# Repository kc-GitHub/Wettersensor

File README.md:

Firmware for Univarsal Wettersensor (Neue Firmware based on the current new version of NewsAskSin Lib)
===================================

* http://www.fhemwiki.de/wiki/Universalsensor
* http://forum.fhem.de/index.php/topic,20620.0.html

#Changelog#

##Version 1.0 (Development)##
 * Rewritten code based on NewsAskSin

##Version 0.15 (Development)##
 * Improve / Fix debugging.
 * Fix [#16](/../../issues/16) so peering with HM-CC-RT-DN should stable now.
 * Add hysteresis for battery voltage measurement.
 * Experimental support for US-100 ultrasonic distance sensor (Do not use this experimental feature if you need the peering with HM-CC-RT-DN at this time)

##Version 0.14##
 * Fix millis() overflow bug. Now, the sensor stays in sleep mode after 49 days, so battery should not drained anymore
 * Battery voltage now measured with 1 digit only.

##Version 0.13 (Beta)##
 * Add new register:
   - transmitTryMax: How often should the sensor try to send data without ack.
   - lowBatLimit: Defined the battery voltage used for low battery detection.
   - ledMode: Switch the device LED on or off while sent out data.
   - altitude: Define the sensor-altitude for calculating the air pressure at sea level.

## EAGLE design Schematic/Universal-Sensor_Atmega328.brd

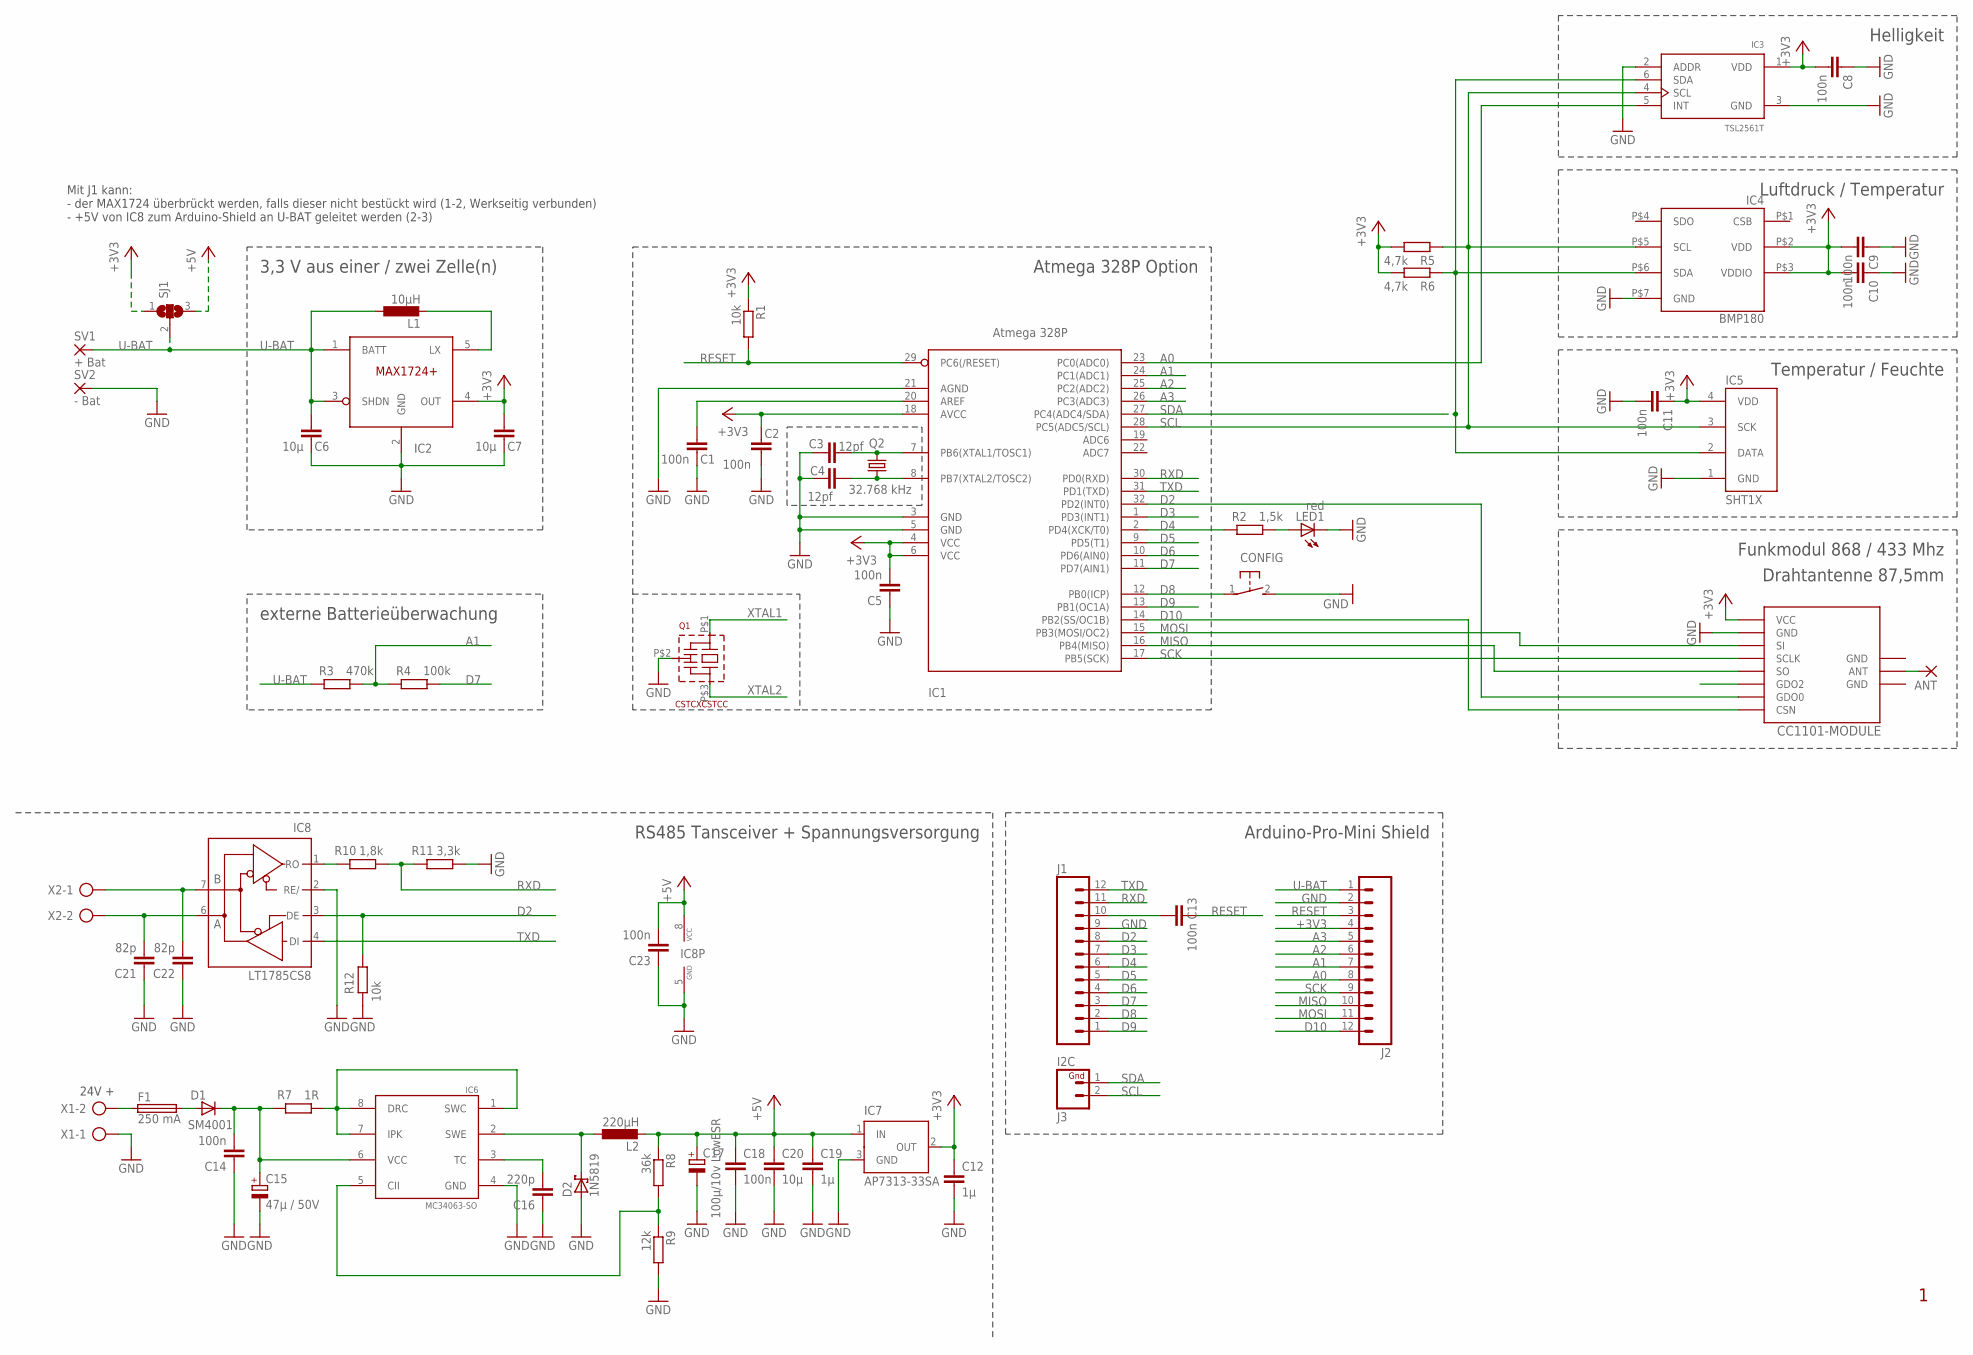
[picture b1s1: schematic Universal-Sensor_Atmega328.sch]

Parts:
ANT: 1,6/0,8
C1, C2, C5, C8, C9, C10, C11, C13, C18, C23: 100n; C0805
C3, C4: 12pf; C0805
C6, C7, C20: 10µ; C1206
C12, C19: 1µ; C0805
C14: 100n; C1206
C15: 47µ / 50V; E2,5-7
C16: 220p; C0805
C17: 100µ/10v LowESR; SMC_D
C21, C22: 82p; C0805
CC1101-MODULE: CC1101_WIRELES_MODULE
CONFIG: DTSM-3
D1: SM4001; MELF-MLL41
D2: 1N5819; SMB
F1: 250 mA; SMD-6,1X2,6
IC1: Atmega 328P; TQFP32-08
IC2: MAX1724; SOT23-5L
IC3: TSL2561T; TMB-6
IC4: BMP180; LGA-7
IC5: SHT1X
IC6: MC34063-SO; SO8
IC7: AP7313-33SA; SOT23
IC8: LT1785CS8; SO08
J1, J2: M12PTH; 1X12
J3: I2C; 1X02
L1: 10µH; L4532P
L2: 220µH; L5650M
LED1: red; CHIP-LED0805
Q1: CSTCXCSTCC; CSTCC
Q2: 32.768 kHz; TC38H
R1, R12: 10k; M0805
R2: 1,5k; M0805
R3: 470k; M0805
R4: 100k; M0805
R5, R6: 4,7k; M0805
R7: 1R; R0805
R8: 36k; R0805
R9: 12k; R0805
R10: 1,8k; R0805
R11: 3,3k; R0805
SJ1: SJ2W; SJ_2
SV1: + Bat; 1,6/0,9
SV2: - Bat; 1,6/0,9
X1, X2: AK550/2

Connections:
+3V3: C2.2, C5.2, C7.2, C8.2, C9.2, C10.2, C11.1, C12.1, CC1101-MODULE.VCC, IC1.4 (VCC), IC1.6 (VCC), IC1.18 (AVCC), IC2.4 (OUT), IC3.1 (VDD), IC4.P$2 (VDD), IC4.P$3 (VDDIO), IC5.4 (VDD), IC7.2 (OUT), J2.4, R1.1, R5.2, R6.2, SJ1.1
+5V: C17.+, C18.1, C19.1, C20.1, C23.2, IC7.1 (IN), IC8.8 (VCC), L2.2, R8.1, SJ1.3
A: C21.2, IC8.6 (A), X2.2
A0: IC1.23 (PC0(ADC0)), IC3.5 (INT), J2.8
A1: IC1.24 (PC1(ADC1)), J2.7, R3.2, R4.1
A2: IC1.25 (PC2(ADC2)), J2.6
A3: IC1.26 (PC3(ADC3)), J2.5
B: C22.2, IC8.7 (B), X2.1
D2: CC1101-MODULE.GDO0, IC1.32 (PD2(INT0)), IC8.3 (DE), J1.8, R12.2
D3: IC1.1 (PD3(INT1)), J1.7
D4: IC1.2 (PD4(XCK/T0)), J1.6, R2.1
D5: IC1.9 (PD5(T1)), J1.5
D6: IC1.10 (PD6(AIN0)), J1.4
D7: IC1.11 (PD7(AIN1)), J1.3, R4.2
D8: CONFIG.1, IC1.12 (PB0(ICP)), J1.2
D9: IC1.13 (PB1(OC1A)), J1.1
D10: CC1101-MODULE.CSN, IC1.14 (PB2(SS/OC1B)), J2.12
GND: C1.1, C2.1, C3.2, C4.2, C5.1, C6.1, C7.1, C8.1, C9.1, C10.1, C11.2, C12.2, C14.1, C15.-, C16.1, C17.-, C18.2, C19.2, C20.2, C21.1, C22.1, C23.1, CC1101-MODULE.GND@1 (GND), CC1101-MODULE.GND@2 (GND), CC1101-MODULE.GND@3 (GND), CONFIG.2, D2.A, IC1.3 (GND), IC1.5 (GND), IC1.21 (AGND), IC2.2 (GND), IC3.2 (ADDR), IC3.3 (GND), IC4.P$7 (GND), IC5.1 (GND), IC6.4 (GND), IC7.3 (GND), IC8.2 (RE/), IC8.5 (GND), J1.9, J2.2, LED1.C, Q1.P$2 (GND), R9.2, R11.1, R12.1, SV2.1, X1.1
MISO: CC1101-MODULE.SO, IC1.16 (PB4(MISO)), J2.10
MOSI: CC1101-MODULE.SI, IC1.15 (PB3(MOSI/OC2)), J2.11
unnamed: C13.2, J1.10
unnamed: IC2.5 (LX), L1.2
unnamed: LED1.A, R2.2
unnamed: ANT.1, CC1101-MODULE.ANT
unnamed: F1.1, X1.2
unnamed: IC8.1 (RO), R10.2
unnamed: C1.2, IC1.20 (AREF)
unnamed: D1.A, F1.2
unnamed: IC6.1 (SWC), IC6.7 (IPK), IC6.8 (DRC), R7.1
unnamed: C14.2, C15.+, D1.C, IC6.6 (VCC), R7.2
unnamed: IC6.5 (CII), R8.2, R9.1
unnamed: C16.2, IC6.3 (TC)
unnamed: D2.C, IC6.2 (SWE), L2.1
RESET: C13.1, IC1.29 (PC6(/RESET)), J2.3, R1.2
RXD: IC1.30 (PD0(RXD)), J1.11, R10.1, R11.2
SCK: CC1101-MODULE.SCLK, IC1.17 (PB5(SCK)), J2.9
SCL: IC1.28 (PC5(ADC5/SCL)), IC3.4 (SCL), IC4.P$5 (SCL), IC5.3 (SCK), J3.2, R5.1
SDA: IC1.27 (PC4(ADC4/SDA)), IC3.6 (SDA), IC4.P$6 (SDA), IC5.2 (DATA), J3.1, R6.1
TXD: IC1.31 (PD1(TXD)), IC8.4 (DI), J1.12
U-BAT: C6.2, IC2.1 (BATT), IC2.3 (SHDN), J2.1, L1.1, R3.1, SJ1.2, SV1.1
XTAL1: C3.1, IC1.7 (PB6(XTAL1/TOSC1)), Q1.P$1 (1), Q2.2
XTAL2: C4.1, IC1.8 (PB7(XTAL2/TOSC2)), Q1.P$3 (3), Q2.1

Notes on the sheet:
Mit J1 kann: - der MAX1724 überbrückt werden, falls dieser nicht bestückt wird (1-2, Werkseitig verbunden) - +5V von IC8 zum Arduino-Shield an U-BAT geleitet werden (2-3)
24V +
RS485 Tansceiver + Spannungsversorgung
3,3 V aus einer / zwei Zelle(n)
externe Batterieüberwachung
Arduino-Pro-Mini Shield
Atmega 328P Option
Helligkeit
Luftdruck / Temperatur
Temperatur / Feuchte
Funkmodul 868 / 433 Mhz
Drahtantenne 87,5mm
IC2

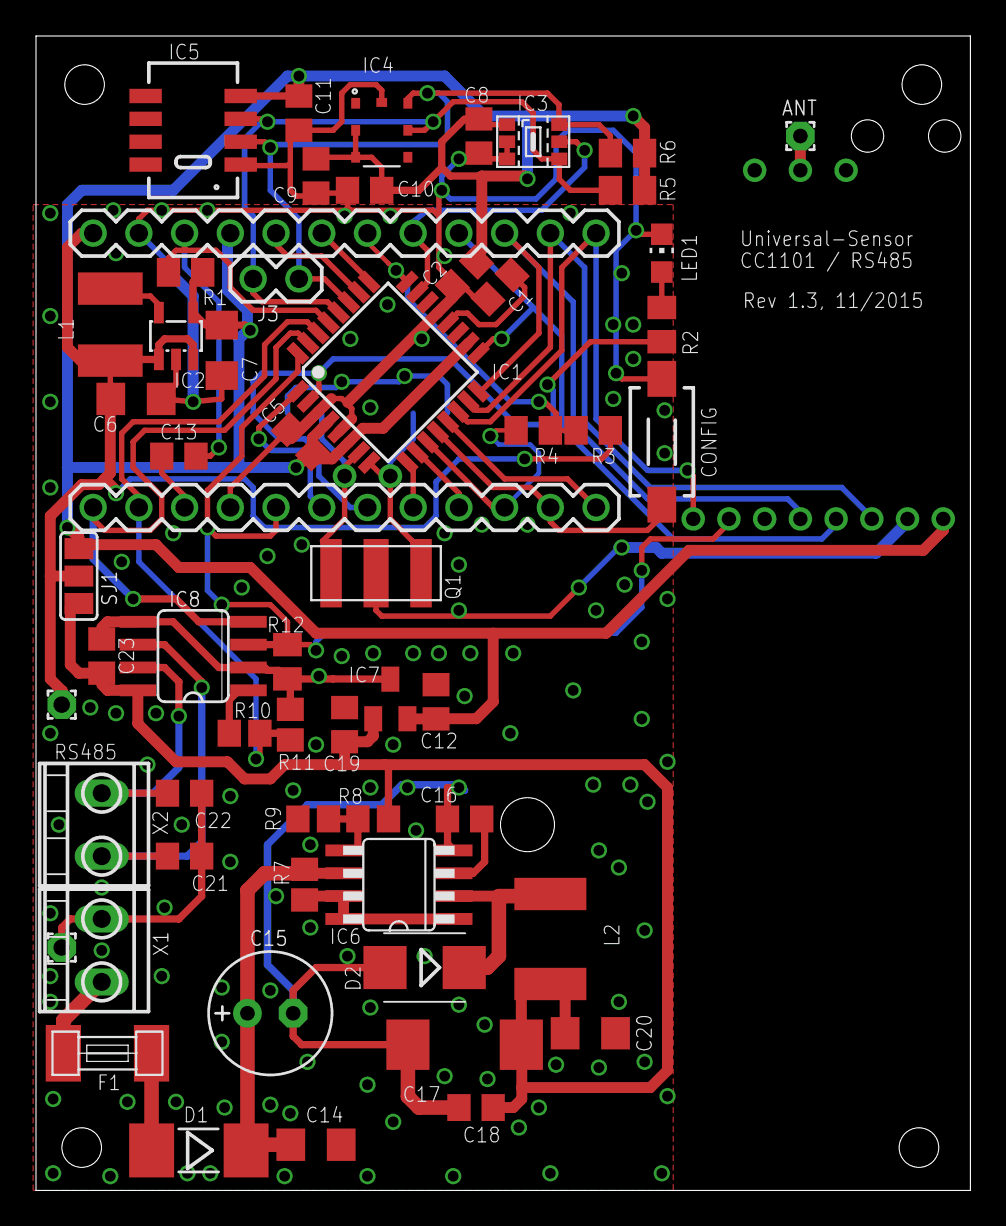
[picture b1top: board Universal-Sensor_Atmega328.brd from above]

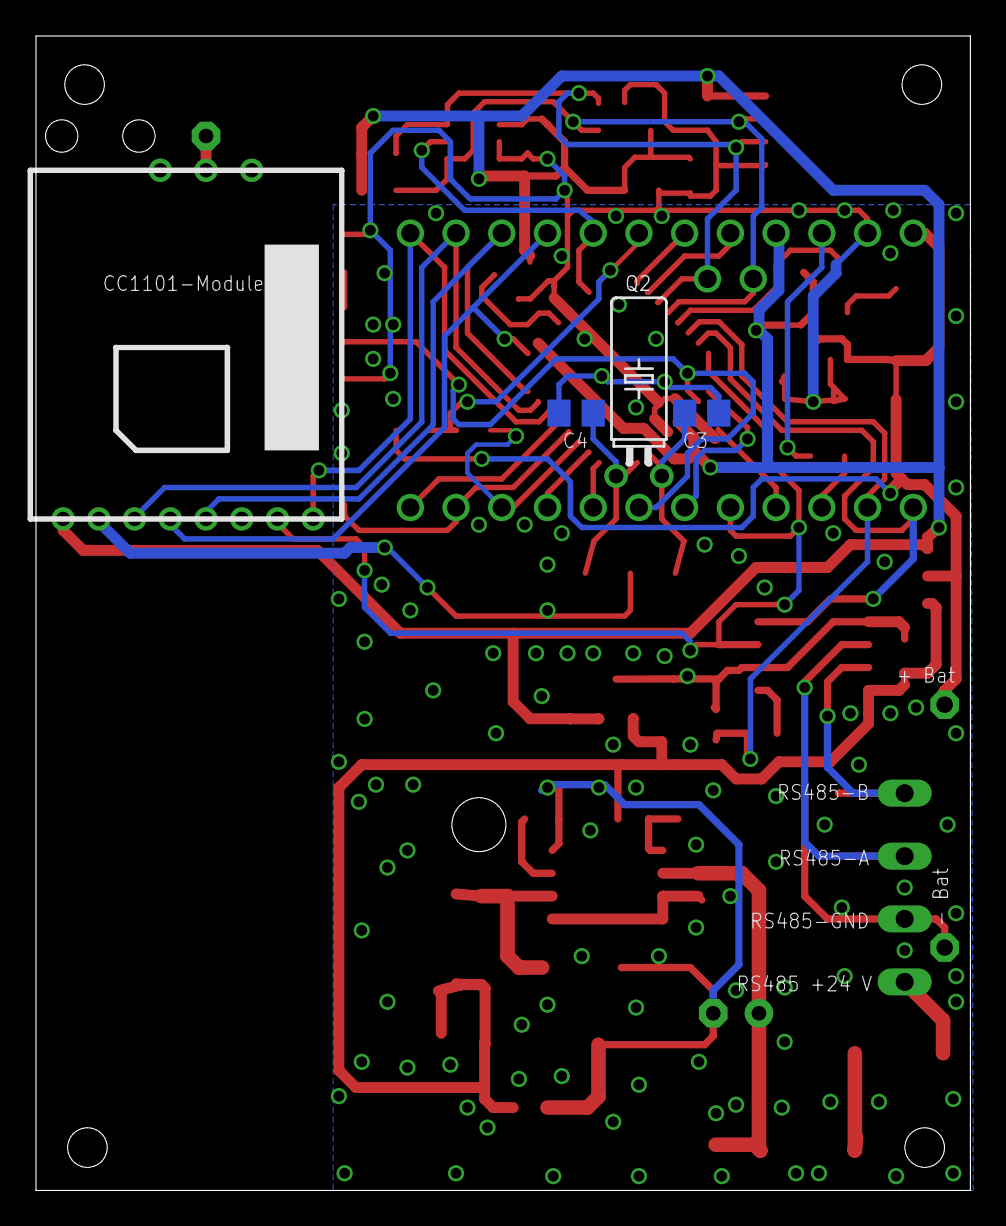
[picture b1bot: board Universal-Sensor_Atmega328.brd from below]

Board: 2 copper layers, 51.9 x 64.1 mm, 62 parts (4 on the bottom side), 42 nets.

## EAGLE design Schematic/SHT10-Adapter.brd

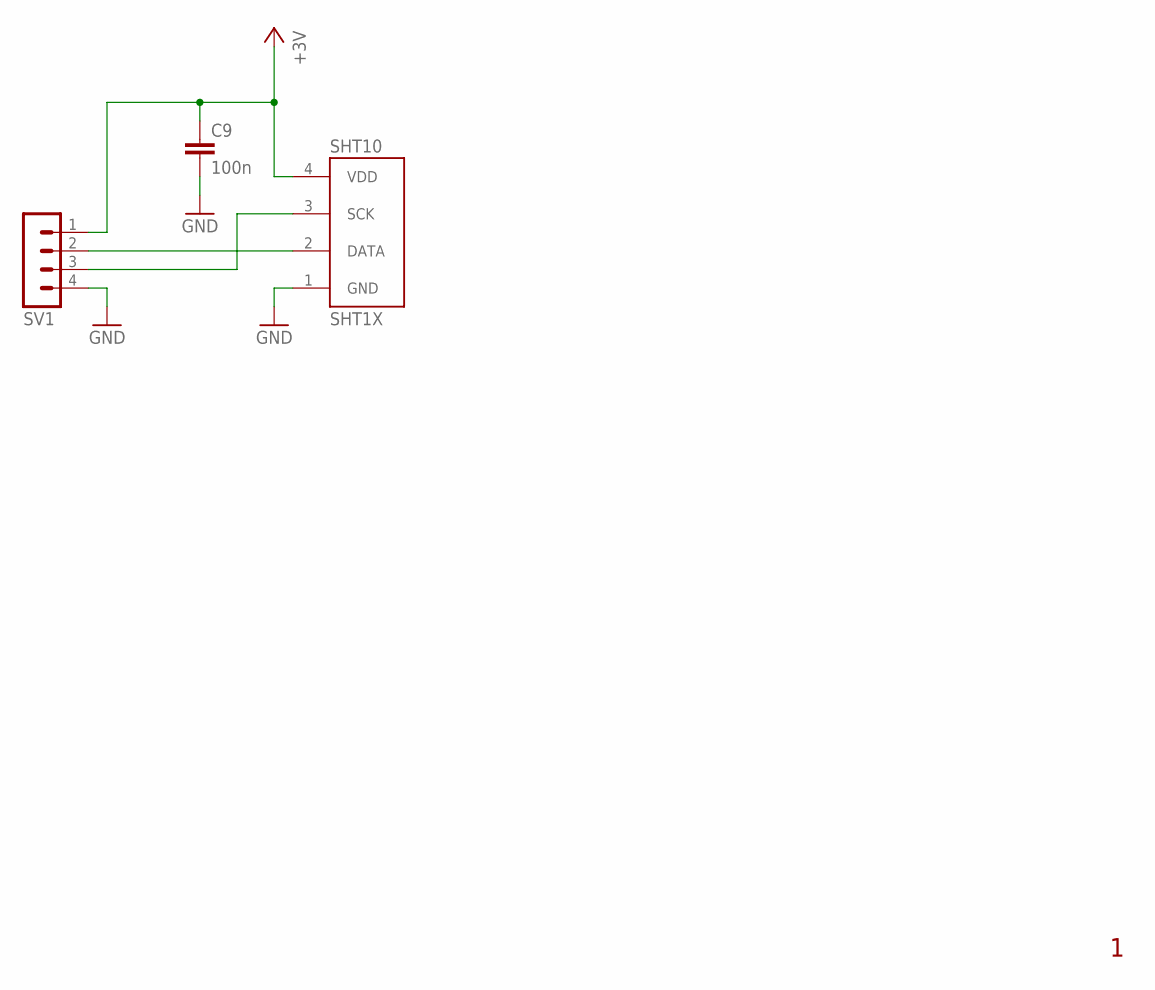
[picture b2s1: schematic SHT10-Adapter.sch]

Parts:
C9: 100n; C0805
SHT10: SHT1X
SV1: MA04-1

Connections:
GND: C9.2, SHT10.1 (GND), SV1.4
SCL: SHT10.3 (SCK), SV1.3
SDA: SHT10.2 (DATA), SV1.2
VCC: C9.1, SHT10.4 (VDD), SV1.1

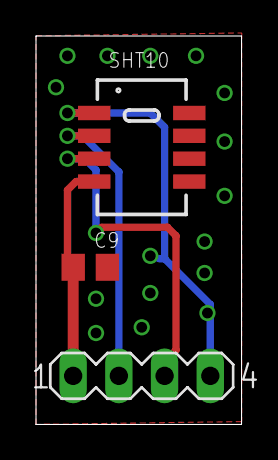
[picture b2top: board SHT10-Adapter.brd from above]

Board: 2 copper layers, 11.4 x 21.6 mm, 3 parts (0 on the bottom side), 4 nets.

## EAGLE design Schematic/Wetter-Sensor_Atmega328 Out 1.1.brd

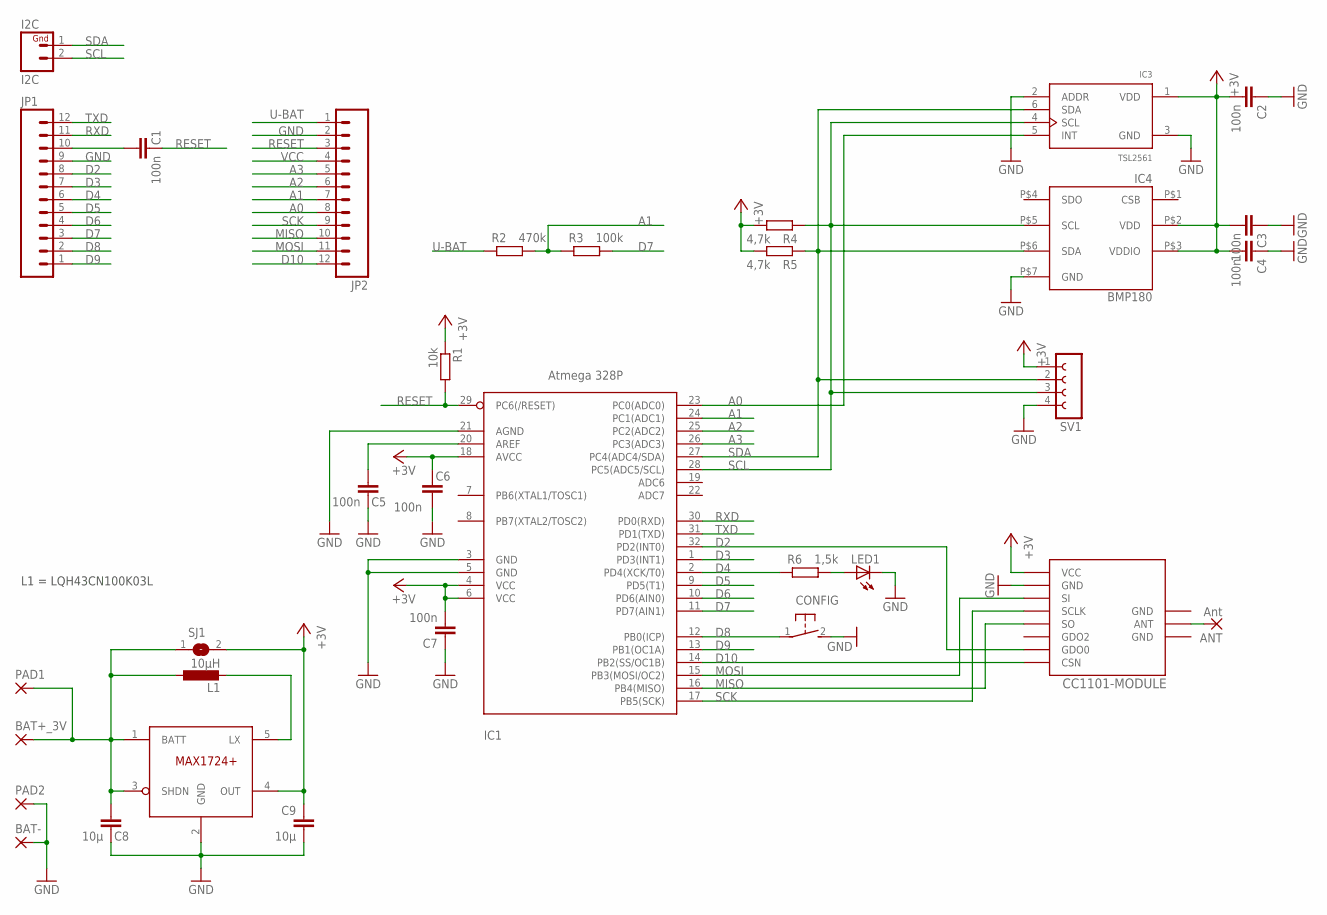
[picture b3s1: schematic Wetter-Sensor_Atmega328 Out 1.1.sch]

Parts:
ANT: Ant; 1,6/0,8
BAT+_3V: 1,6/0,9
BAT-: 1,6/0,9
C1, C2, C3, C4, C5, C6, C7: 100n; C0805
C8, C9: 10µ; C1206
CC1101-MODULE: CC1101_WIRELES_MODULE
CONFIG: DTSM-3
I2C: I2C; 1X02
IC1: Atmega 328P; TQFP32-08
IC2: MAX1724; SOT23-5L
IC3: TSL2561; TMB-6
IC4: BMP180; LGA-7
JP1, JP2: M12PTH; 1X12
L1: 10µH; L4532P
LED1: LEDCHIP-LED0805; CHIP-LED0805
PAD1, PAD2: SMD2; SMD1,27-2,54
R1: 10k; M0805
R2: 470k; M0805
R3: 100k; M0805
R4, R5: 4,7k; M0805
R6: 1,5k; M0805
SJ1: SJ
SV1: FE04-1

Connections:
A0: IC1.23 (PC0(ADC0)), IC3.5 (INT), JP2.8
A1: IC1.24 (PC1(ADC1)), JP2.7, R2.2, R3.1
A2: IC1.25 (PC2(ADC2)), JP2.6
A3: IC1.26 (PC3(ADC3)), JP2.5
D2: CC1101-MODULE.GDO0, IC1.32 (PD2(INT0)), JP1.8
D3: IC1.1 (PD3(INT1)), JP1.7
D4: IC1.2 (PD4(XCK/T0)), JP1.6, R6.1
D5: IC1.9 (PD5(T1)), JP1.5
D6: IC1.10 (PD6(AIN0)), JP1.4
D7: IC1.11 (PD7(AIN1)), JP1.3, R3.2
D8: CONFIG.1, IC1.12 (PB0(ICP)), JP1.2
D9: IC1.13 (PB1(OC1A)), JP1.1
D10: CC1101-MODULE.CSN, IC1.14 (PB2(SS/OC1B)), JP2.12
GND: BAT-.1, C2.1, C3.1, C4.1, C5.1, C6.1, C7.1, C8.1, C9.1, CC1101-MODULE.GND@1 (GND), CC1101-MODULE.GND@2 (GND), CC1101-MODULE.GND@3 (GND), CONFIG.2, IC1.3 (GND), IC1.5 (GND), IC1.21 (AGND), IC2.2 (GND), IC3.2 (ADDR), IC3.3 (GND), IC4.P$7 (GND), JP1.9, JP2.2, LED1.C, PAD2.1, SV1.4
MISO: CC1101-MODULE.SO, IC1.16 (PB4(MISO)), JP2.10
MOSI: CC1101-MODULE.SI, IC1.15 (PB3(MOSI/OC2)), JP2.11
unnamed: C1.2, JP1.10
unnamed: IC2.5 (LX), L1.2
unnamed: LED1.A, R6.2
unnamed: ANT.1, CC1101-MODULE.ANT
unnamed: C5.2, IC1.20 (AREF)
RESET: C1.1, IC1.29 (PC6(/RESET)), JP2.3, R1.2
RXD: IC1.30 (PD0(RXD)), JP1.11
SCK: CC1101-MODULE.SCLK, IC1.17 (PB5(SCK)), JP2.9
SCL: I2C.2, IC1.28 (PC5(ADC5/SCL)), IC3.4 (SCL), IC4.P$5 (SCL), R4.1, SV1.3
SDA: I2C.1, IC1.27 (PC4(ADC4/SDA)), IC3.6 (SDA), IC4.P$6 (SDA), R5.1, SV1.2
TXD: IC1.31 (PD1(TXD)), JP1.12
U-BAT: BAT+_3V.1, C8.2, IC2.1 (BATT), IC2.3 (SHDN), JP2.1, L1.1, PAD1.1, R2.1, SJ1.1
VCC: C2.2, C3.2, C4.2, C6.2, C7.2, C9.2, CC1101-MODULE.VCC, IC1.4 (VCC), IC1.6 (VCC), IC1.18 (AVCC), IC2.4 (OUT), IC3.1 (VDD), IC4.P$2 (VDD), IC4.P$3 (VDDIO), JP2.4, R1.1, R4.2, R5.2, SJ1.2, SV1.1

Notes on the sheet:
L1 = LQH43CN100K03L

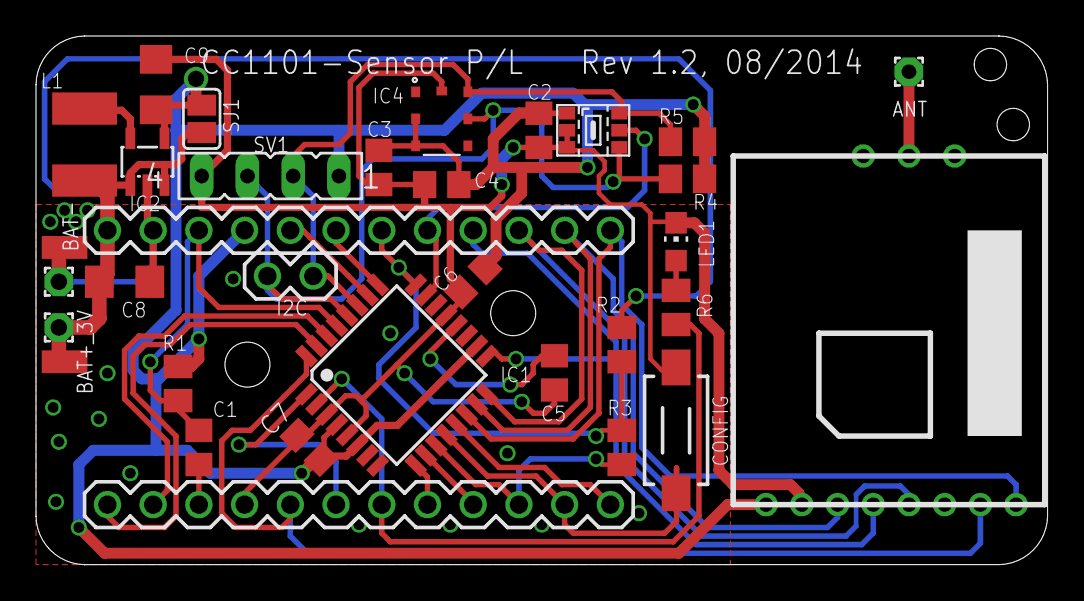
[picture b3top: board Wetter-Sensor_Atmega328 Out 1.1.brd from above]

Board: 2 copper layers, 56.2 x 29.4 mm, 33 parts (0 on the bottom side), 29 nets.

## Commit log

2014-04-09 setup repo
2014-04-09 Version 0.5
2014-04-09 add Flash-Tool
2014-04-10 add missing file to flash tool
2014-04-10 add modifyed bootloader: Support for Blinking the led while flashing, handle watchdog resets correctly.
2014-04-10 Prevent the bootloader from clearing the MCUSR register. The programm sould know the reset reason to.
2014-04-11 cleanup
2014-04-11 Version 0.6
2014-04-12 extension for adding own device types for FHEM
2014-04-12 new Version 0.6 with own device type
2014-04-13 add Flash-Tool-Windows.zip
2014-04-14 Version 0.7, fix value if no brightness sensor available
2014-04-14 submodule update
2014-04-18 add addon for CCU 1 or CCU 2 to use the sensor
2014-04-18 change model name, add second model for outdoor version, update CCU-Addon, update FHEM module
2014-04-19 Version 0.8
2014-04-19 change typos
2014-04-19 change reading for luminosity and remove unity
2014-04-24 fix charset + update_script
2014-05-01 add flash tool for linux (Raspbyery Pi)
2014-05-06 small fix in update script
2014-05-08 bugfix in bootloader
2014-05-11 add schematic
2014-05-16 fix wrong tar format
2014-05-16 update-script fix
2014-05-19 important bugfix
2014-06-19 adding spaces in if conditions
2014-07-13 update AskSin subrepo
2014-07-13 change resend count to 5, change firmware version von 0.10
2014-07-14 update flash tool tgz and zip
2014-07-18 update schematic
2014-08-09 now address data we can get from bootloader section. must not stored in program section anymore, some optimations
2014-08-09 add submodule for AskSin OTA Bootloader
2014-08-09 remove test files
2014-08-13 update subrepos
2014-09-13 fix bug, so the sht10 now can messure temperaturs below 0 °C
2014-09-19 reduce "air pressure now send with 1 digit precision.
2014-09-19 update subrepo
2014-09-20 fix TSL2561::setInterruptThreshold
2014-09-20 add some defines
2014-09-21 Firmware V0.12
2014-09-22 update culHmSubTypeSets, add fwUpdate, getSerial
2014-09-25 fix reset command
2014-09-25 remove old debug functions
2014-10-02 raise version to 0.13 (developper version)
2014-10-02 add register for low battery limit, led mode
2014-10-03 add register transmitTryMax and altitude to calculate air pressure at sea level
2014-10-03 add compiled firmare files, update project structure
2014-10-06 change min low battery voltage to 1.0 V, update xml-files for ccu, update firmware
2014-10-06 add some utilities
2014-10-08 fix ccu xml files
2014-10-09 fix ccu xml files again
2015-02-24 small bugfix in TSL2561::writeUInt
2015-02-24 add #ifndef _REGISTER_h
2015-02-24 add some images
2015-02-26 update AskSin lib
2015-02-26 small changes
2015-02-26 fix bugs, so the code compiles with the arduion ide 1.6.0
2015-02-26 update battery measurement factor
2015-02-27 fix register.h if USE_ADRESS_SECTION==0
2015-02-27 increase battery measuring intervall to 15 minutes
2015-03-01 Version 0.14 (Beta)
2015-03-03 Fix / Rework debugging
2015-03-03 new development version 0.15
2015-03-05 fix ccu addon
2015-03-05 add lazy config option
2015-03-06 update lib for #11
2015-04-04 add v0.15 firmware files
2015-09-23 add Eagle files
2015-10-13 fix updatescript for low ccu1 filesystem space
2015-10-23 fix for USE_ADRESS_SECTION=0, add experimental support for US-100 ultra sonic distance sensor
2015-10-24 Update changelog
2015-12-14 update board file
2016-02-13 add fhem control file
2017-01-26 add expermental code in AskSin lib for reading ultrasinic sensor US-100 or read from avr's adc channel
2017-02-02 Begin rewrite firmware on base of NewAskSin lib
2017-02-02 add excel sheet Battery-Energyconsumption.xls
2017-02-02 change sensor send slot
2017-02-02 change powermode to sleep
2017-02-02 load register settings on startup
2017-02-03 Some optimisations Fix TSL2561 initialize because of too much power consumption
2017-02-03 fix send slot calculation
2017-02-03 change config button behavior: short send sensor data immediately, long: config
2017-02-03 Fix in sendtiming Feature: send data immediately after press device button Changed: for config, device button mit hold long Merge NewAskSin-Lib
2017-02-04 change some timings, hold config button down after bootloader, before device start to change config button behavior

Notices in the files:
parts and their libraries:
eagle-library-edeca.net-v5: This is v1 and is licensed under the Creative Commons (Attribution-Non-Commercial-Share Alike 2.0 UK)
